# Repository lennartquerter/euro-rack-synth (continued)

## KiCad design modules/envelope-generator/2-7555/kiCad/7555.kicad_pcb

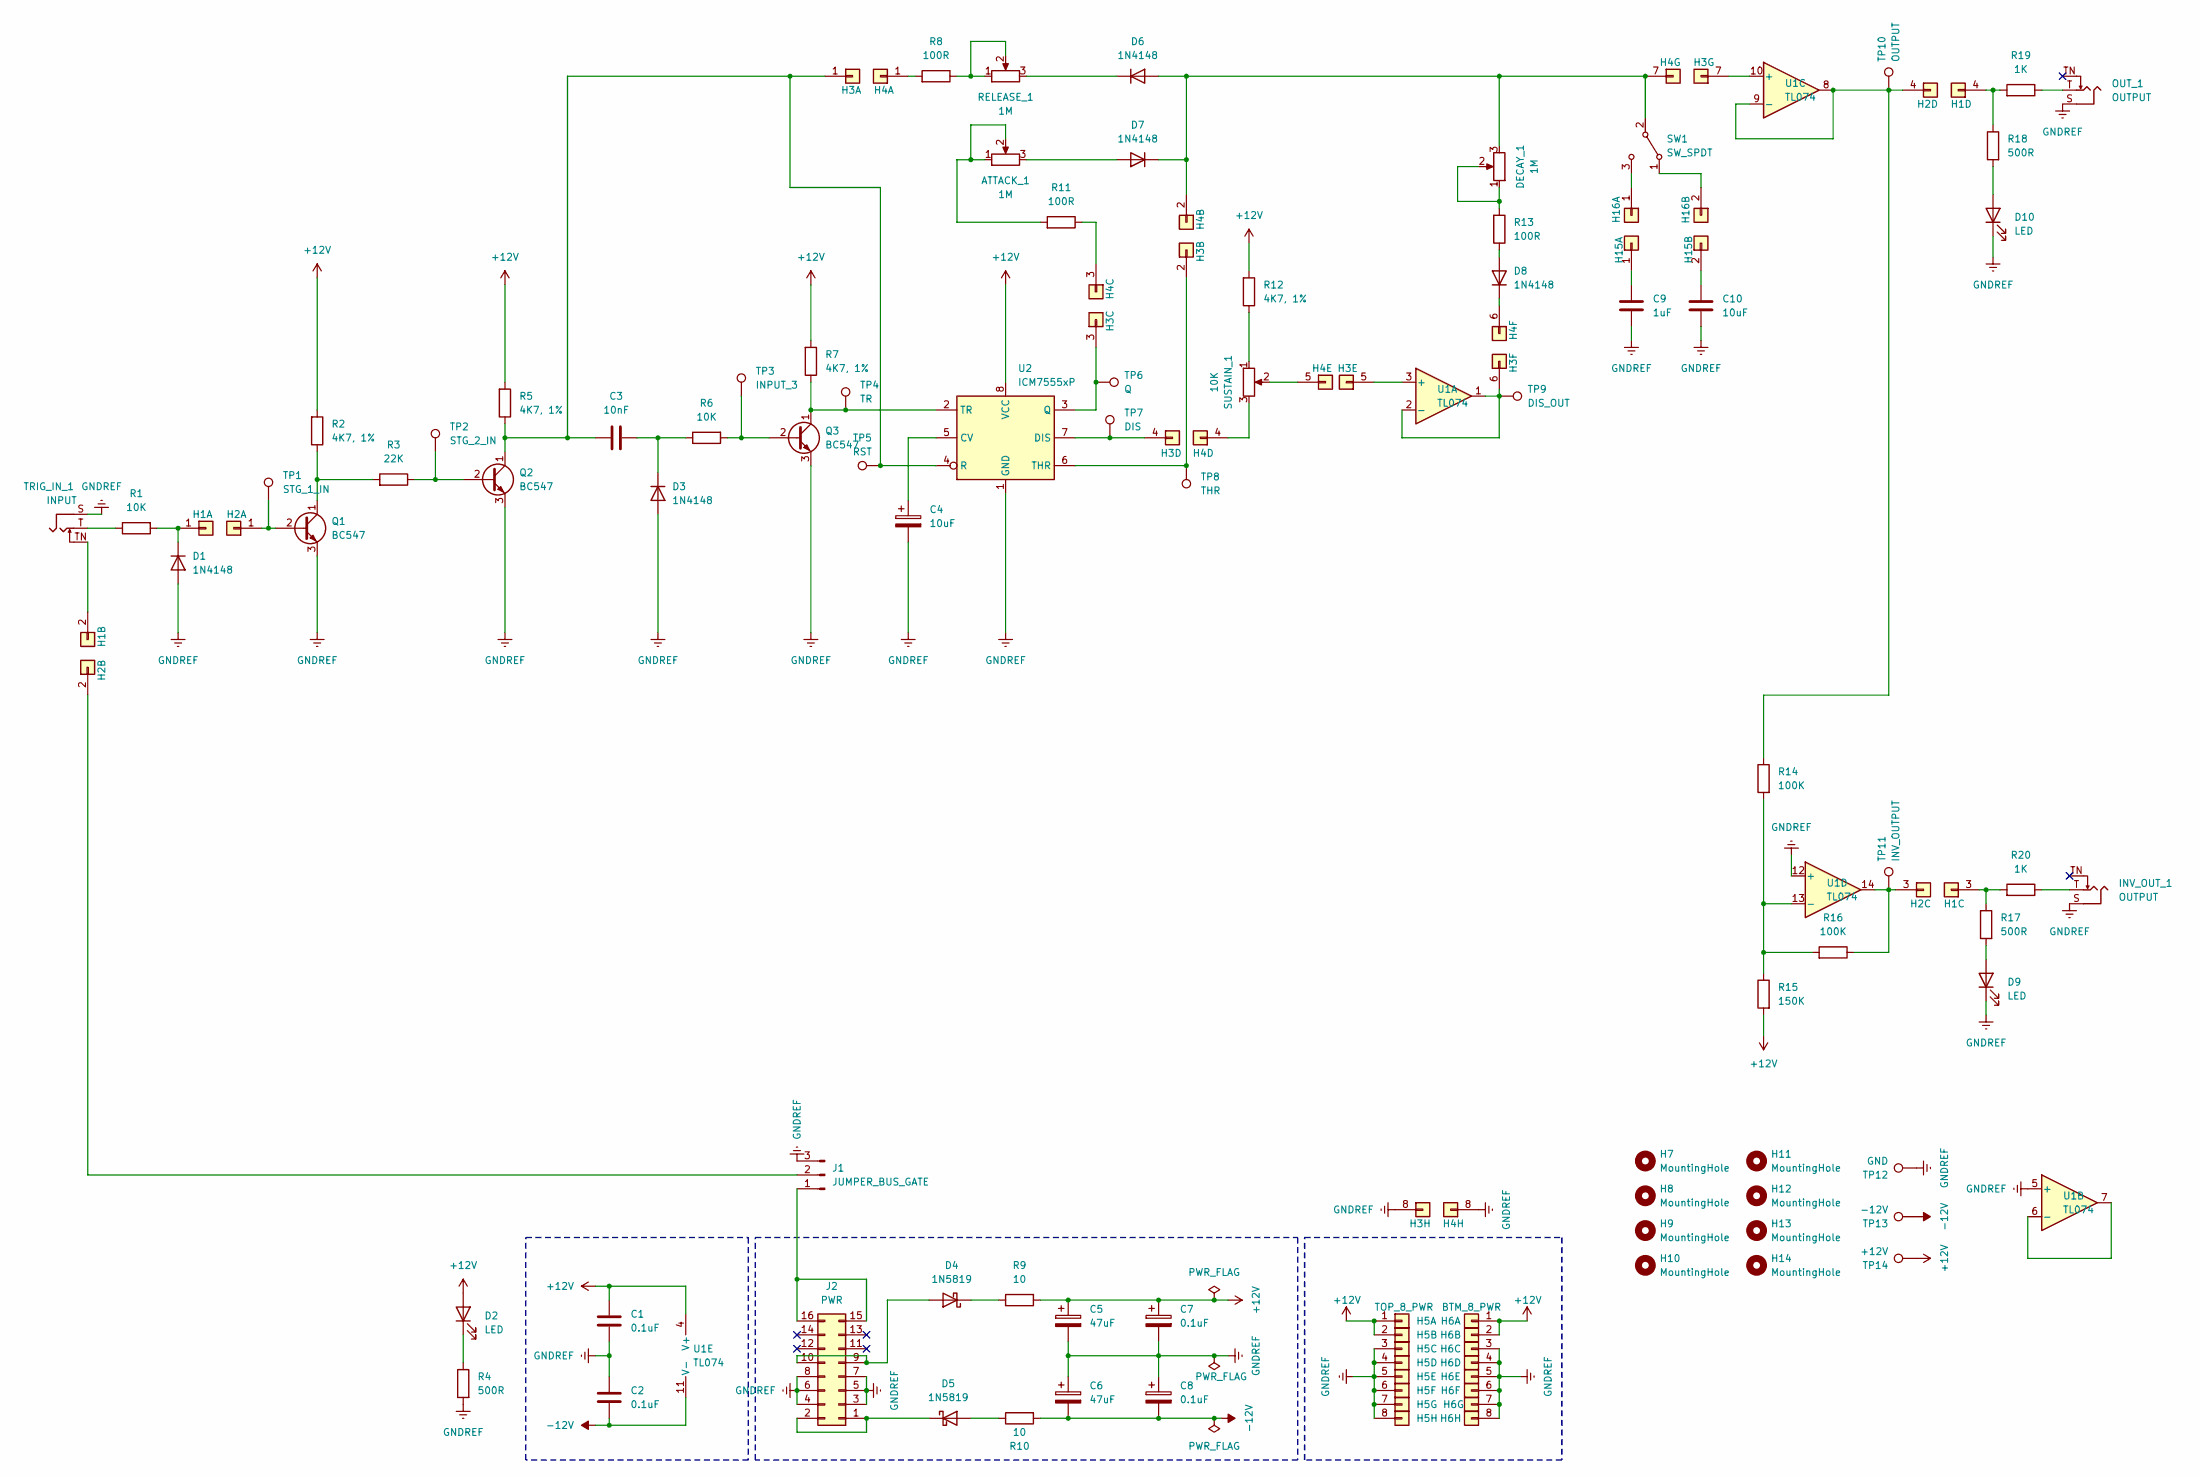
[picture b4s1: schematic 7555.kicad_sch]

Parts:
ATTACK_1: 1M; Potentiometer_TT_P0915N
C1, C2: 0.1uF; C_Disc_D5.0mm_W2.5mm_P5.00mm
C3: 10nF; C_RECT_WIMA_0.1uF
C4: 10uF; CP_Radial_D6.3mm_P2.50mm
C5, C6: 47uF; CP_Radial_D6.3mm_P2.50mm
C7, C8: 0.1uF; CP_Radial_D4.0mm_P2.00mm
C9: 1uF; C_RECT_MKT_1uF
C10: 10uF; C_RECT_MKT_1uF
D1, D3, D6, D7, D8: 1N4148; D_DO-35_SOD27_P7.62mm_Horizontal
D2, D9, D10: LED; LED_D5.0mm (center Aligned)
D4, D5: 1N5819; D_DO-41_SOD81_P10.16mm_Horizontal
DECAY_1: 1M; Potentiometer_TT_P0915N
H1: TOP_4_SGL; PinHeader_1x04_P2.54mm_Vertical
H2: BTM_4_SGL; PinSocket_1x04_P2.54mm_Vertical
H3: BTM_8_SGL; PinSocket_1x08_P2.54mm_Vertical
H4: TOP_8_SGL; PinHeader_1x08_P2.54mm_Vertical
H5: TOP_8_PWR; PinHeader_1x08_P2.54mm_Vertical
H6: BTM_8_PWR; PinSocket_1x08_P2.54mm_Vertical
H7, H8, H9, H10, H11, H12, H13, H14: MountingHole; MountingHole_3.2mm_M3
H15: PinHeader_01x02; PinSocket_1x02_P2.54mm_Vertical
H16: PinSocket_01x02; PinHeader_1x02_P2.54mm_Vertical
INV_OUT_1: OUTPUT; Jack_3.5mm_QingPu_WQP-PJ398SM_Vertical_CircularHoles
J1: JUMPER_BUS_GATE; PinHeader_1x03_P2.54mm_Vertical
J2: PWR; IDC-Header_2x08_P2.54mm_Vertical
OUT_1: OUTPUT; Jack_3.5mm_QingPu_WQP-PJ398SM_Vertical_CircularHoles
Q1, Q2, Q3: BC547; TO-92_HandSolder
R1, R6: 10K; R_Default (DIN0207)
R2, R5, R7, R12: 4K7, 1%; R_Default (DIN0207)
R3: 22K; R_Default (DIN0207)
R4, R17, R18: 500R; R_Default (DIN0207)
R8, R11, R13: 100R; R_Default (DIN0207)
R9, R10: 10; R_Default (DIN0207)
R14, R16: 100K; R_Default (DIN0207)
R15: 150K; R_Default (DIN0207)
R19, R20: 1K; R_Default (DIN0207)
RELEASE_1: 1M; Potentiometer_TT_P0915N
SUSTAIN_1: 10K; Potentiometer_TT_P0915N
SW1: SW_SPDT; SW_default
TP1: STG_1_IN; Pin_D1.0mm_L10.0mm
TP2: STG_2_IN; Pin_D1.0mm_L10.0mm
TP3: INPUT_3; Pin_D1.0mm_L10.0mm
TP4: TR; Pin_D1.0mm_L10.0mm
TP5: RST; Pin_D1.0mm_L10.0mm
TP6: Q; Pin_D1.0mm_L10.0mm
TP7: DIS; Pin_D1.0mm_L10.0mm
TP8: THR; Pin_D1.0mm_L10.0mm
TP9: DIS_OUT; Pin_D1.0mm_L10.0mm
TP10: OUTPUT; Pin_D1.0mm_L10.0mm
TP11: INV_OUTPUT; Pin_D1.0mm_L10.0mm
TP12: GND; Pin_D1.0mm_L10.0mm
TP13: -12V; Pin_D1.0mm_L10.0mm
TP14: +12V; Pin_D1.0mm_L10.0mm
TRIG_IN_1: INPUT; Jack_3.5mm_QingPu_WQP-PJ398SM_Vertical_CircularHoles
U1: TL074; DIP-14_W7.62mm_Socket_LongPads
U2: ICM7555xP; DIP-8_W7.62mm

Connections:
+12V: C1.1, C5.1, C7.1, D2.2 (A), H5.1, H5.2, H6.1 (Pin_3), H6.2, R2.1, R5.1, R7.1, R9.1, R12.1, R15.1, TP14.1, U1.4 (V+), U2.8 (VCC)
-12V: C2.2, C6.2, C8.2, R10.1, TP13.1, U1.11 (V-)
GNDREF: C1.2, C2.1, C4.2, C5.2, C6.1, C7.2, C8.1, C9.2, C10.2, D1.2 (A), D3.2 (A), D9.1 (K), D10.1 (K), H3.8, H4.8, H5.3, H5.4, H5.5, H5.6, H5.7, H5.8, H6.3, H6.4, H6.5, H6.6, H6.7, H6.8, INV_OUT_1.S, J1.3, J2.3 (GND), J2.4 (GND), J2.5 (GND), J2.6 (GND), J2.7 (GND), J2.8 (GND), OUT_1.S, Q1.3 (E), Q2.3 (E), Q3.3 (E), R4.1, TP12.1, TRIG_IN_1.S, U1.5 (+), U1.12 (+), U2.1 (GND)
unnamed: ATTACK_1.1, ATTACK_1.2, R11.1
unnamed: D1.1 (K), H1.1, R1.1
unnamed: D2.1 (K), R4.2
unnamed: C3.2, D3.1 (K), R6.2
unnamed: D4.2 (A), J2.9 (+12V), J2.10 (+12V)
unnamed: D4.1 (K), R9.2
unnamed: D5.2 (A), R10.2
unnamed: D5.1 (K), J2.1 (-12V), J2.2 (-12V)
unnamed: D6.2 (A), D7.1 (K), DECAY_1.3, H4.2, H4.7, SW1.2 (B)
unnamed: D6.1 (K), RELEASE_1.3
unnamed: ATTACK_1.3, D7.2 (A)
unnamed: D8.2 (A), R13.2
unnamed: D8.1 (K), H4.6
unnamed: D9.2 (A), R17.1
unnamed: D10.2 (A), R18.1
unnamed: DECAY_1.1, DECAY_1.2, R13.1
unnamed: H1.2, TRIG_IN_1.TN
unnamed: H1.3, R17.2, R20.1
unnamed: H1.4, R18.2, R19.1
unnamed: H2.1, Q1.2 (B), TP1.1
unnamed: H2.2, J1.2
unnamed: H2.3, R16.2, TP11.1, U1.14
unnamed: H2.4, R14.2, TP10.1, U1.8, U1.9 (-)
unnamed: C3.1, H3.1 (Pin_3), Q2.1 (C), R5.2, TP5.1, U2.4 (R)
unnamed: H3.2, TP8.1, U2.6 (THR)
unnamed: H3.3, TP6.1, U2.3 (Q)
unnamed: H3.4, TP7.1, U2.7 (DIS)
unnamed: H3.5, U1.3 (+)
unnamed: H3.6, TP9.1, U1.1, U1.2 (-)
unnamed: H3.7, U1.10 (+)
unnamed: H4.1, R8.1
unnamed: H4.3, R11.2
unnamed: H4.4, SUSTAIN_1.3
unnamed: H4.5, SUSTAIN_1.2
unnamed: C9.1, H15.1
unnamed: C10.1, H15.2
unnamed: H16.1, SW1.3 (C)
unnamed: H16.2, SW1.1 (A)
unnamed: INV_OUT_1.T, R20.2
unnamed: J1.1, J2.15 (GATE), J2.16 (GATE)
unnamed: OUT_1.T, R19.2
unnamed: Q1.1 (C), R2.2, R3.1
unnamed: Q2.2 (B), R3.2, TP2.1
unnamed: Q3.2 (B), R6.1, TP3.1
unnamed: Q3.1 (C), R7.2, TP4.1, U2.2 (TR)
unnamed: R1.2, TRIG_IN_1.T
unnamed: R8.2, RELEASE_1.1, RELEASE_1.2
unnamed: R12.2, SUSTAIN_1.1
unnamed: U1.6 (-), U1.7
unnamed: R14.1, R15.2, R16.1, U1.13 (-)
unnamed: C4.1, U2.5 (CV)

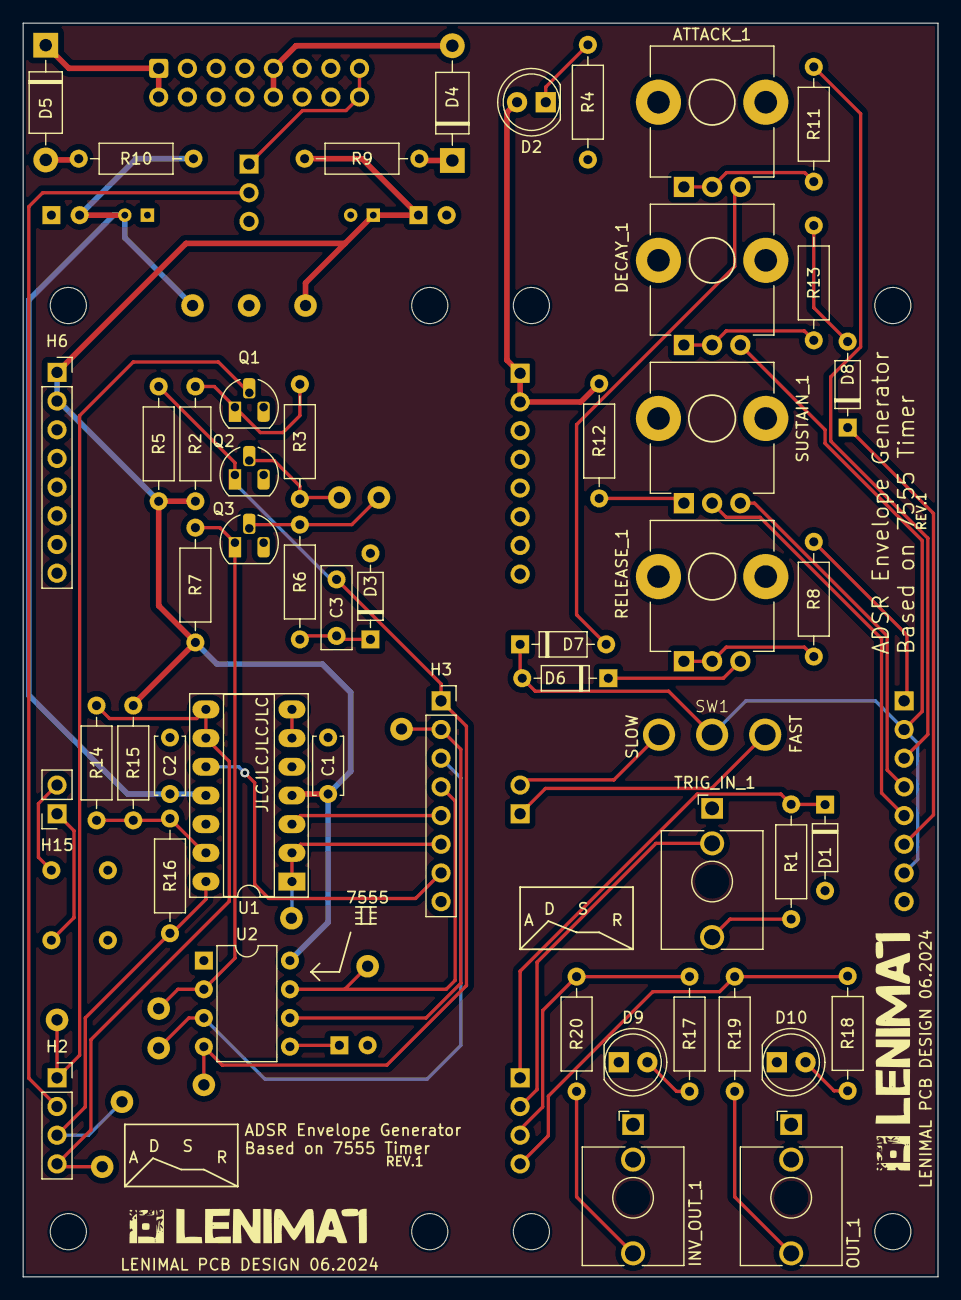
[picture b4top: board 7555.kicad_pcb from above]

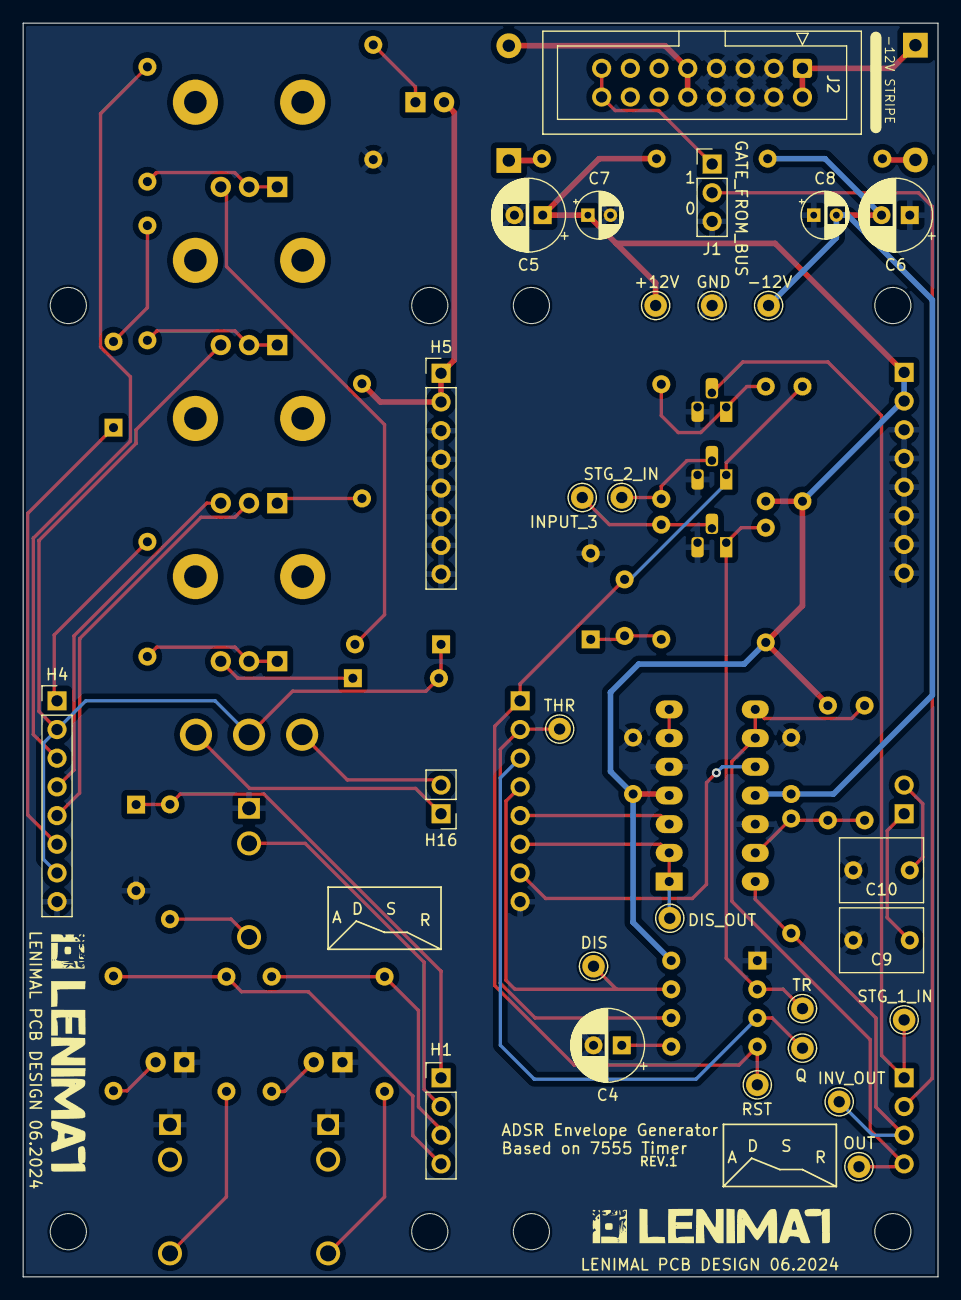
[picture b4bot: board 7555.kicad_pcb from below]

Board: 2 copper layers, 81.0 x 111.0 mm, 85 parts (27 on the bottom side), 54 nets.

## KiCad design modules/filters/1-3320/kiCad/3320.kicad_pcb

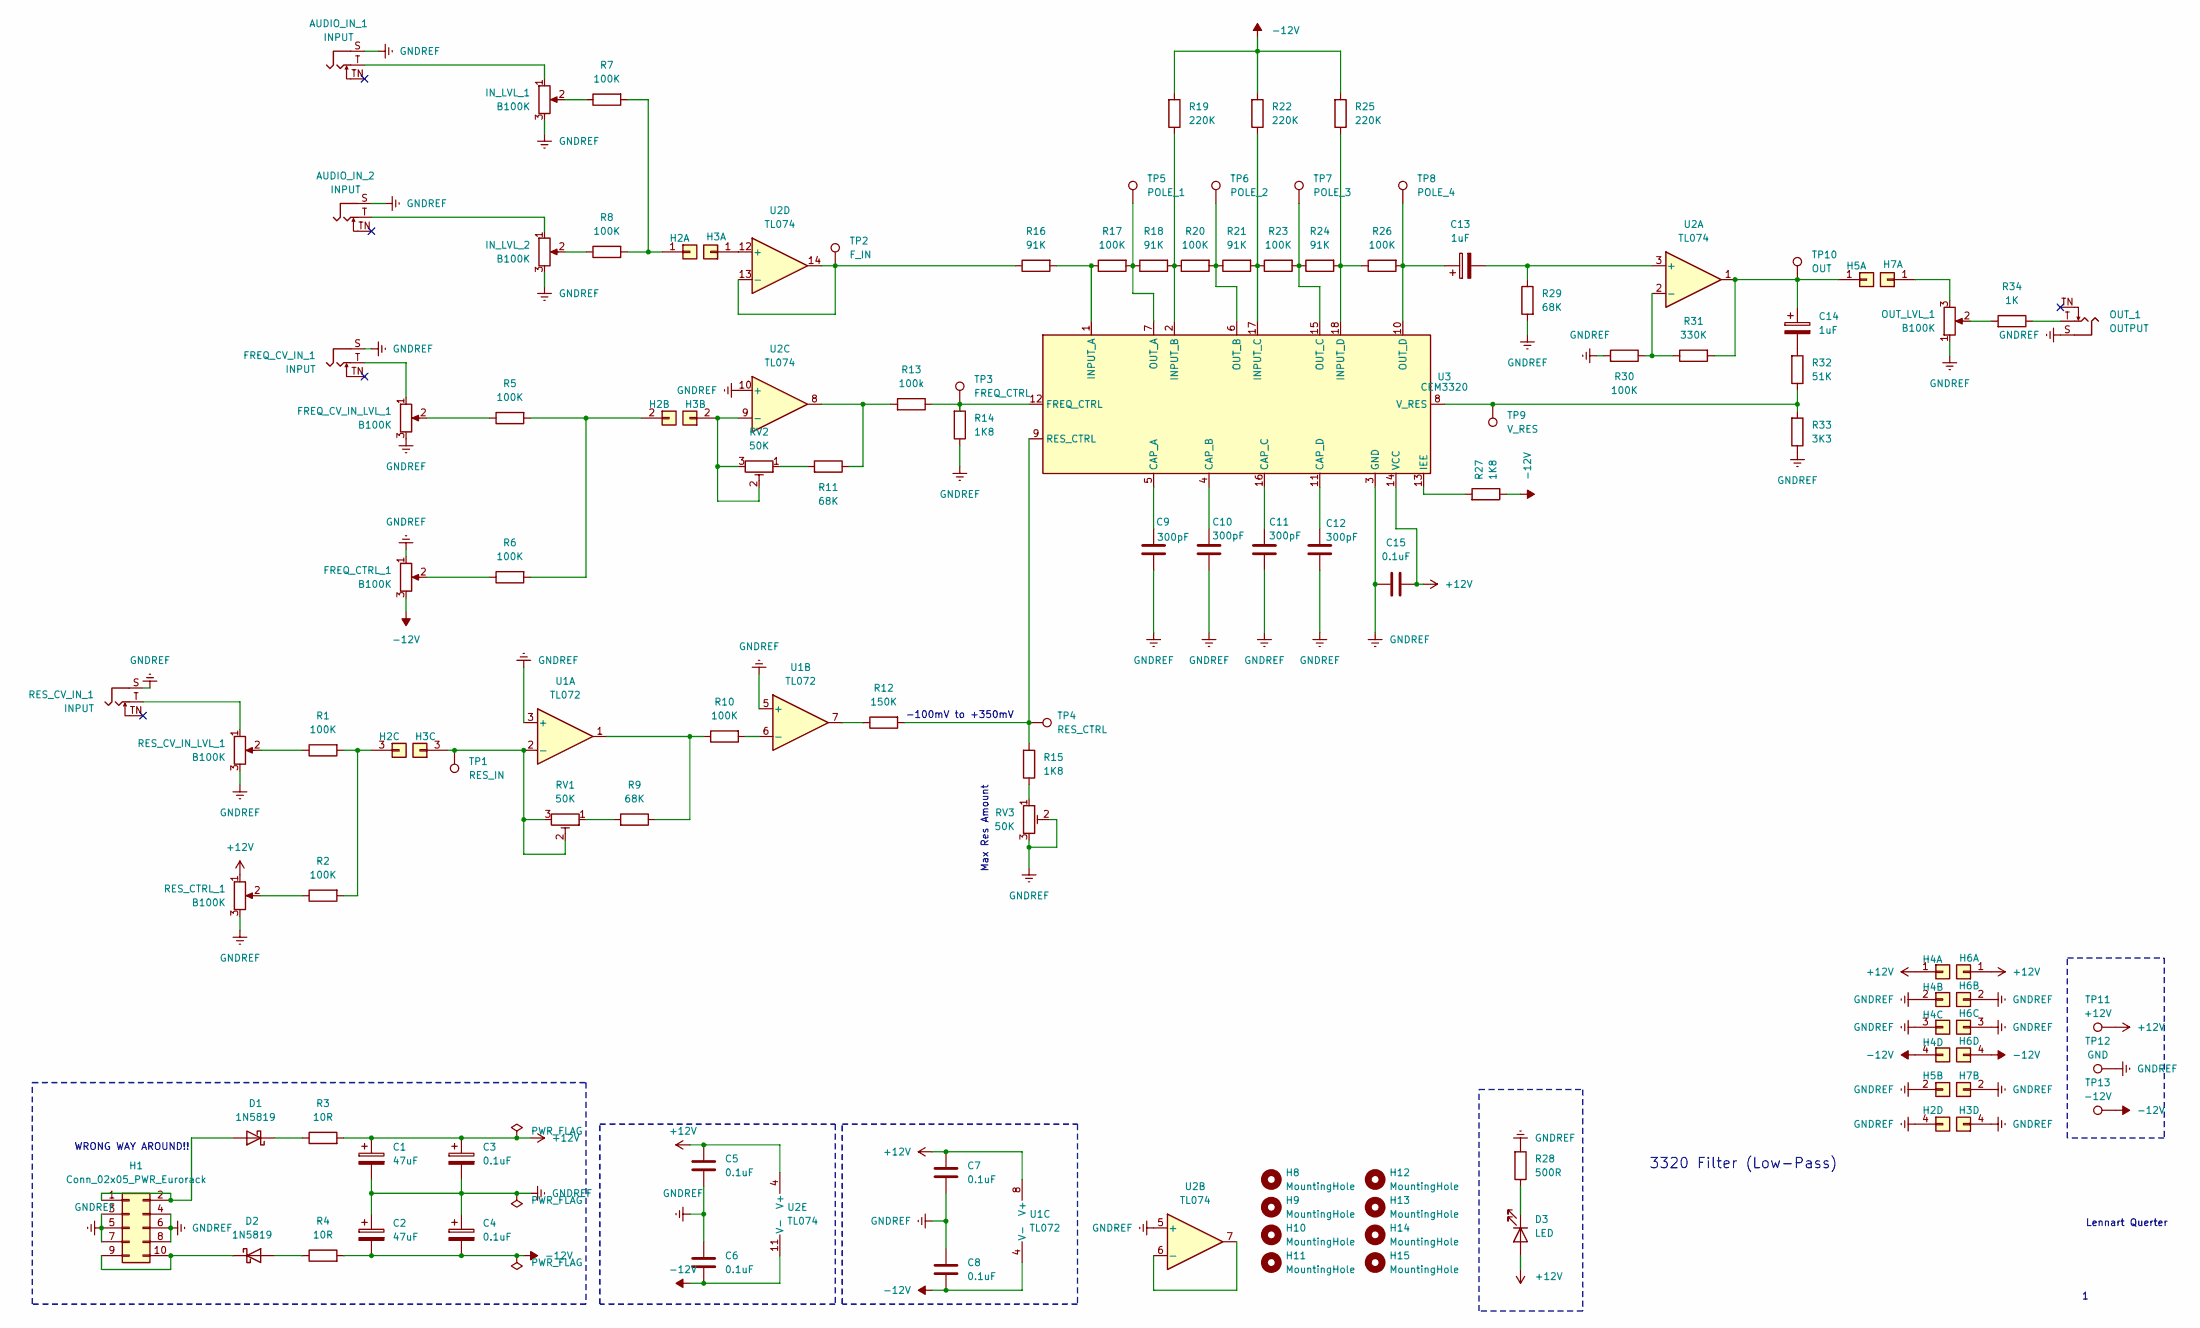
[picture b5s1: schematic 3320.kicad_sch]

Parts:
AUDIO_IN_1, AUDIO_IN_2: INPUT; Jack_3.5mm_QingPu_WQP-PJ398SM_Vertical_CircularHoles
C1, C2: 47uF; CP_Radial_D6.3mm_P2.50mm
C3, C4: 0.1uF; CP_Radial_D4.0mm_P2.00mm
C5, C6, C7, C8, C15: 0.1uF; C_Rect_L4.6mm_W2.0mm_P2.50mm_MKS02_FKP02
C9, C10, C11, C12: 300pF; C_RECT_WIMA_0.1uF
C13, C14: 1uF; CP_Radial_D4.0mm_P2.00mm
D1, D2: 1N5819; D_DO-41_SOD81_P10.16mm_Horizontal
D3: LED; LED_D5.0mm (center Aligned)
FREQ_CTRL_1: B100K; Potentiometer_TT_P0915N
FREQ_CV_IN_1: INPUT; Jack_3.5mm_QingPu_WQP-PJ398SM_Vertical_CircularHoles
FREQ_CV_IN_LVL_1: B100K; Potentiometer_Alpha_RD901F-40-00D_Single_Vertical_CircularH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
H1: Conn_02x05_PWR_Eurorack; IDC-Header_2x05_P2.54mm_Vertical
H2, H4: PinHeader_01x04; PinHeader_1x04_P2.54mm_Vertical
H3, H6: PinSocket_01x04; PinSocket_1x04_P2.54mm_Vertical
H5: PinSocket_1x02; PinSocket_1x02_P2.54mm_Vertical
H7: PinHeader_1x02; PinHeader_1x02_P2.54mm_Vertical
H8, H9, H10, H11, H12, H13, H14, H15: MountingHole; MountingHole_3.2mm_M3
IN_LVL_1, IN_LVL_2: B100K; Potentiometer_Alpha_RD901F-40-00D_Single_Vertical_CircularH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
OUT_1: OUTPUT; Jack_3.5mm_QingPu_WQP-PJ398SM_Vertical_CircularHoles
OUT_LVL_1: B100K; Potentiometer_Alpha_RD901F-40-00D_Single_Vertical_CircularH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
R1, R2, R5, R6, R7, R8, R10, R17, R20, R23, R26, R30: 100K; R_Default (DIN0207)
R3, R4: 10R; R_Default (DIN0207)
R9, R11, R29: 68K; R_Default (DIN0207)
R12: 150K; R_Default (DIN0207)
R13: 100k; R_Default (DIN0207)
R14, R15, R27: 1K8; R_Default (DIN0207)
R16, R18, R21, R24: 91K; R_Default (DIN0207)
R19, R22, R25: 220K; R_Default (DIN0207)
R28: 500R; R_Default (DIN0207)
R31: 330K; R_Default (DIN0207)
R32: 51K; R_Default (DIN0207)
R33: 3K3; R_Default (DIN0207)
R34: 1K; R_Default (DIN0207)
RES_CTRL_1: B100K; Potentiometer_TT_P0915N
RES_CV_IN_1: INPUT; Jack_3.5mm_QingPu_WQP-PJ398SM_Vertical_CircularHoles
RES_CV_IN_LVL_1: B100K; Potentiometer_Alpha_RD901F-40-00D_Single_Vertical_CircularH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
RV1, RV2, RV3: 50K; Potentiometer_Bourns_3296W_Vertical
TP1: RES_IN; Pin_D1.0mm_L10.0mm
TP2: F_IN; Pin_D1.0mm_L10.0mm
TP3: FREQ_CTRL; Pin_D1.0mm_L10.0mm
TP4: RES_CTRL; Pin_D1.0mm_L10.0mm
TP5: POLE_1; Pin_D1.0mm_L10.0mm
TP6: POLE_2; Pin_D1.0mm_L10.0mm
TP7: POLE_3; Pin_D1.0mm_L10.0mm
TP8: POLE_4; Pin_D1.0mm_L10.0mm
TP9: V_RES; Pin_D1.0mm_L10.0mm
TP10: OUT; Pin_D1.0mm_L10.0mm
TP11: +12V; Pin_D1.0mm_L10.0mm
TP12: GND; Pin_D1.0mm_L10.0mm
TP13: -12V; Pin_D1.0mm_L10.0mm
U1: TL072; DIP-8_W7.62mm_Socket_LongPads
U2: TL074; DIP-14_W7.62mm_Socket_LongPads
U3: CEM3320; DIP-18_W7.62mm_Socket_LongPads

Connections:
+12V: C1.1, C3.1, C5.1, C7.1, C15.2, D3.2 (A), H4.1, H6.1, R3.2, RES_CTRL_1.1, TP11.1, U1.8 (V+), U2.4 (V+), U3.14 (VCC)
-12V: C2.2, C4.2, C6.2, C8.2, FREQ_CTRL_1.3, H4.4, H6.4, R4.2, R19.1, R22.1, R25.1, R27.2, TP13.1, U1.4 (V-), U2.11 (V-)
GNDREF: AUDIO_IN_1.S, AUDIO_IN_2.S, C1.2, C2.1, C3.2, C4.1, C5.2, C6.1, C7.2, C8.1, C9.1, C10.1, C11.1, C12.1, C15.1, FREQ_CTRL_1.1, FREQ_CV_IN_1.S, FREQ_CV_IN_LVL_1.3, H1.3, H1.4, H1.5, H1.6, H1.7, H1.8, H2.4, H3.4, H4.2, H4.3, H5.2, H6.2, H6.3, H7.2, IN_LVL_1.3, IN_LVL_2.3, OUT_1.S, OUT_LVL_1.1, R14.2, R28.1, R29.1, R30.1, R33.2, RES_CTRL_1.3, RES_CV_IN_1.S, RES_CV_IN_LVL_1.3, RV3.2, RV3.3, TP12.1, U1.3 (+), U1.5 (+), U2.5 (+), U2.10 (+), U3.3 (GND)
unnamed: AUDIO_IN_1.T, IN_LVL_1.1
unnamed: AUDIO_IN_2.T, IN_LVL_2.1
unnamed: C14.2, R32.1
unnamed: D1.2 (A), H1.1, H1.2
unnamed: D1.1 (K), R3.1
unnamed: D2.2 (A), R4.1
unnamed: D2.1 (K), H1.9, H1.10
unnamed: D3.1 (K), R28.2
unnamed: FREQ_CTRL_1.2, R6.2
unnamed: FREQ_CV_IN_1.T, FREQ_CV_IN_LVL_1.1
unnamed: FREQ_CV_IN_LVL_1.2, R5.2
unnamed: H2.1, R7.1, R8.1
unnamed: H2.2, R5.1, R6.1
unnamed: H2.3, R1.1, R2.1
unnamed: H3.1, U2.12 (+)
unnamed: H3.2, RV2.2, RV2.3, U2.9 (-)
unnamed: H3.3, RV1.2, RV1.3, TP1.1, U1.2 (-)
unnamed: C14.1, H5.1, R31.1, TP10.1, U2.1
unnamed: H7.1, OUT_LVL_1.3
unnamed: IN_LVL_1.2, R7.2
unnamed: IN_LVL_2.2, R8.2
unnamed: OUT_1.T, R34.2
unnamed: OUT_LVL_1.2, R34.1
unnamed: R1.2, RES_CV_IN_LVL_1.2
unnamed: R2.2, RES_CTRL_1.2
unnamed: R9.1, RV1.1
unnamed: R9.2, R10.2, U1.1
unnamed: R11.1, RV2.1
unnamed: R11.2, R13.1, U2.8
unnamed: R12.2, U1.7
unnamed: R15.2, RV3.1
unnamed: RES_CV_IN_1.T, RES_CV_IN_LVL_1.1
unnamed: R10.1, U1.6 (-)
unnamed: C13.2, R29.2, U2.3 (+)
unnamed: R30.2, R31.2, U2.2 (-)
unnamed: U2.6 (-), U2.7
unnamed: R16.2, TP2.1, U2.13 (-), U2.14
unnamed: C9.2, U3.5 (CAP_A)
unnamed: C10.2, U3.4 (CAP_B)
unnamed: C11.2, U3.16 (CAP_C)
unnamed: C12.2, U3.11 (CAP_D)
unnamed: R13.2, R14.1, TP3.1, U3.12 (FREQ_CTRL)
unnamed: R27.1, U3.13 (IEE)
unnamed: R16.1, R17.2, U3.1 (INPUT_A)
unnamed: R18.1, R19.2, R20.2, U3.2 (INPUT_B)
unnamed: R21.1, R22.2, R23.2, U3.17 (INPUT_C)
unnamed: R24.1, R25.2, R26.2, U3.18 (INPUT_D)
unnamed: R17.1, R18.2, TP5.1, U3.7 (OUT_A)
unnamed: R20.1, R21.2, TP6.1, U3.6 (OUT_B)
unnamed: R23.1, R24.2, TP7.1, U3.15 (OUT_C)
unnamed: C13.1, R26.1, TP8.1, U3.10 (OUT_D)
unnamed: R12.1, R15.1, TP4.1, U3.9 (RES_CTRL)
unnamed: R32.2, R33.1, TP9.1, U3.8 (V_RES)

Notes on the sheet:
Max Res Amount
WRONG WAY AROUND!!
Lennart Querter
-100mV to +350mV
3320 Filter (Low-Pass)

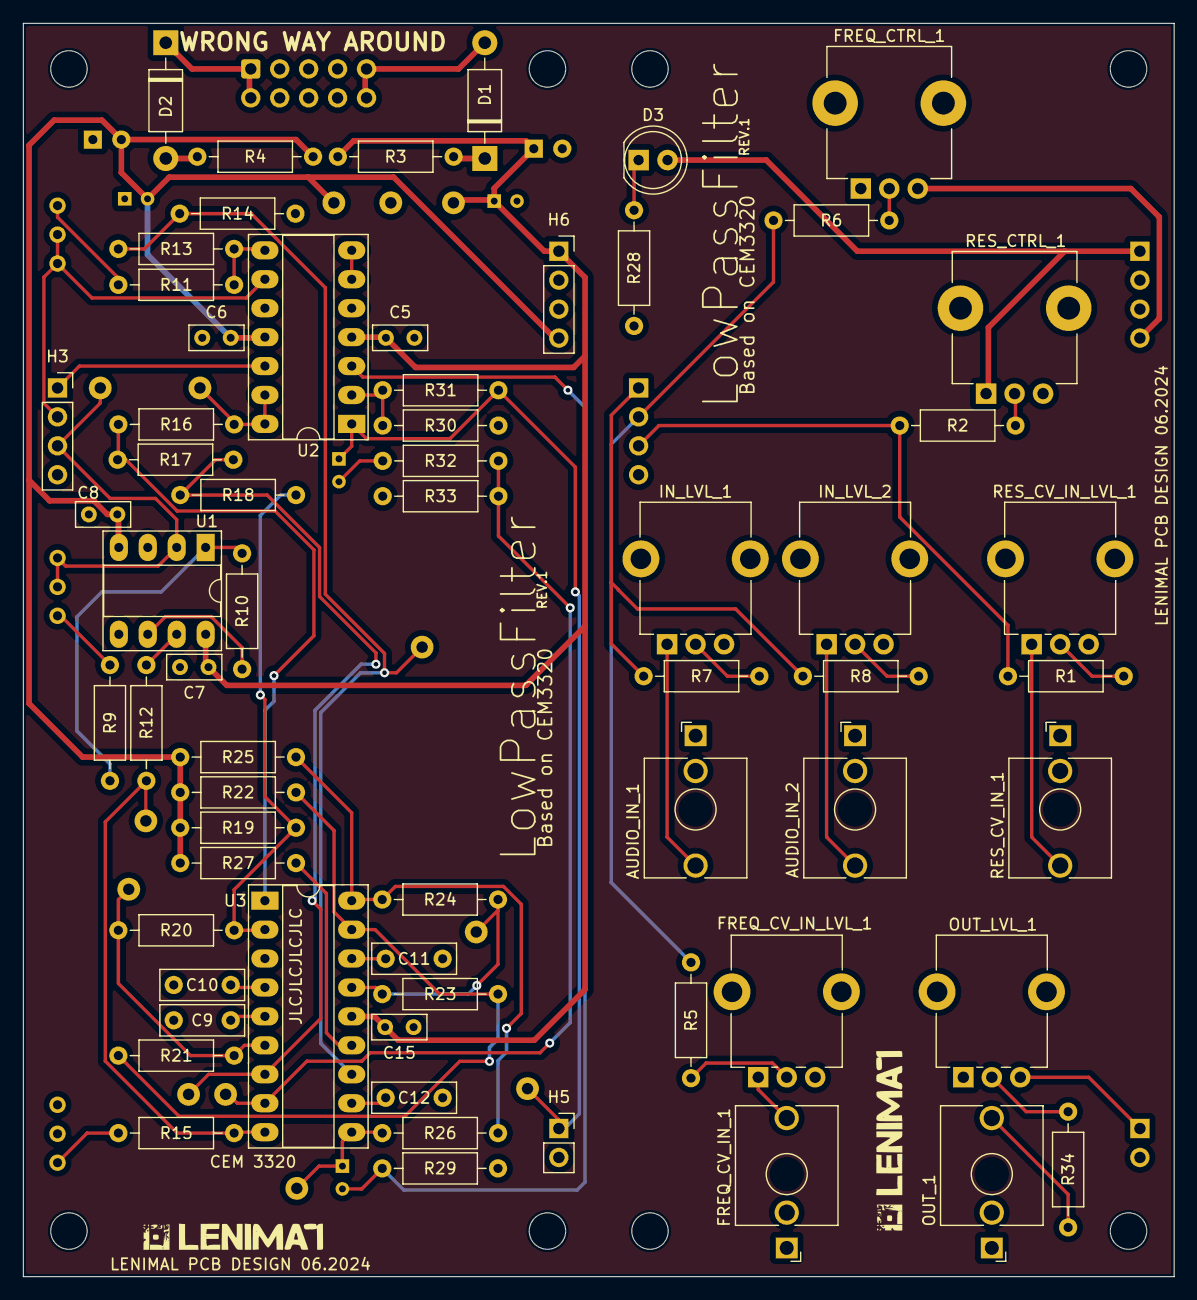
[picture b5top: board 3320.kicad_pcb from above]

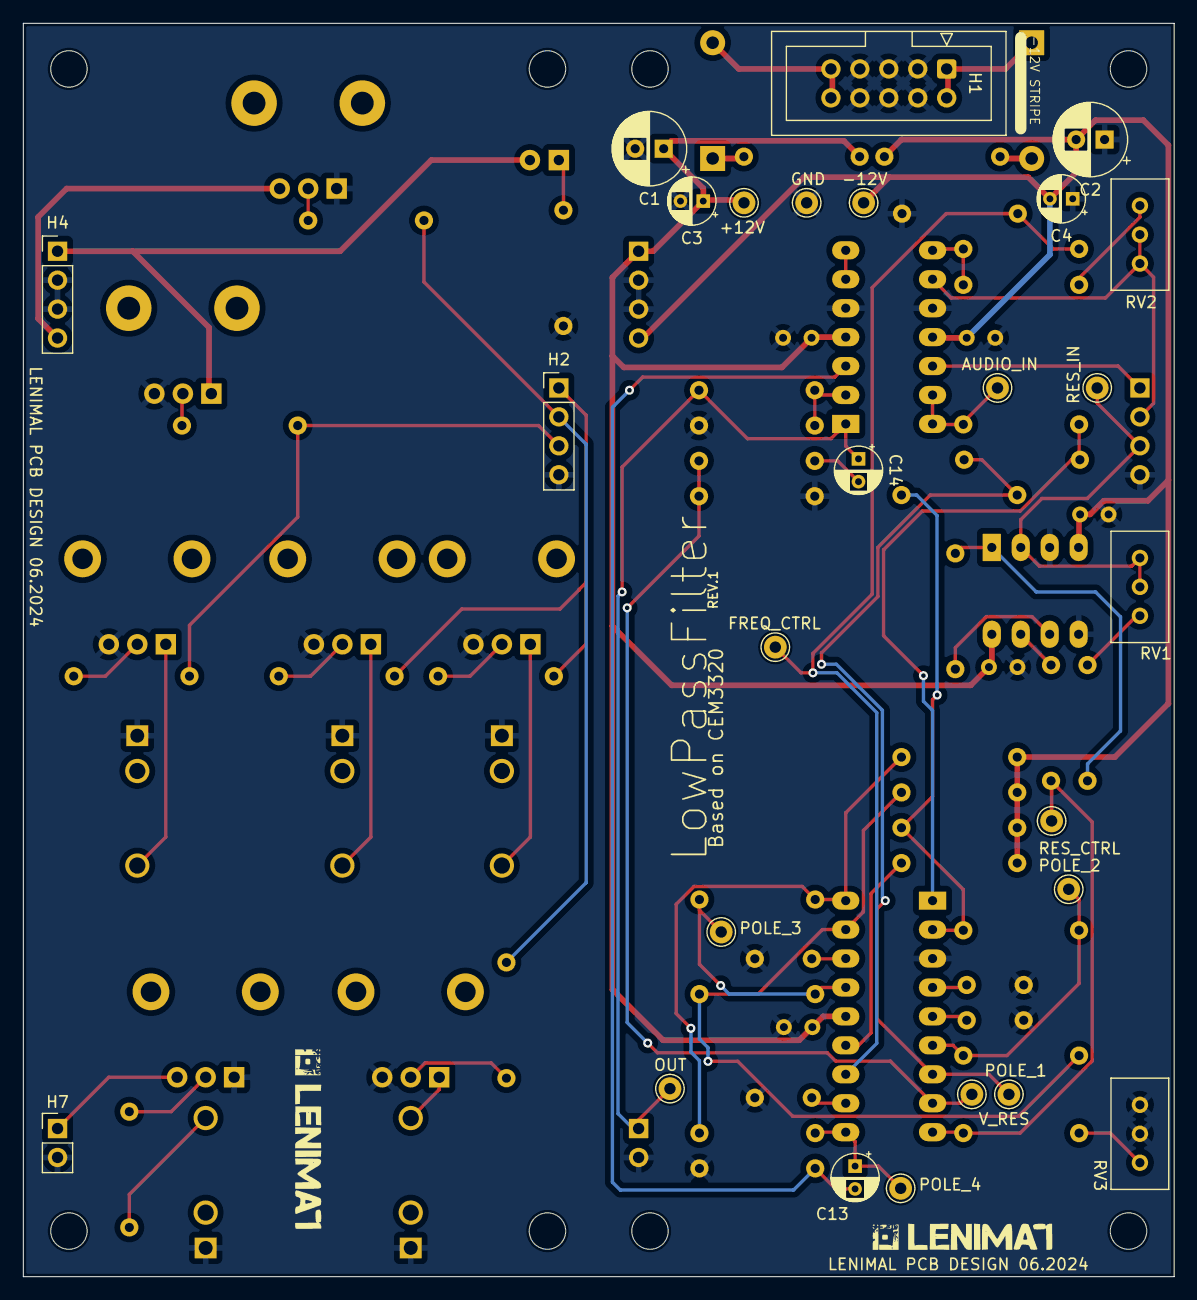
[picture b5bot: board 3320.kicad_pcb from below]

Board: 2 copper layers, 101.0 x 110.0 mm, 98 parts (26 on the bottom side), 56 nets.
